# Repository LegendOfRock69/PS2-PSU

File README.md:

## PS2-PSU
The PS2-PSU is a custom regulator solution meant for powering Playstation 2 Slims that have had an Advanced Trim performed to them or untrimmed consoles with the existing power regulatory components removed.

## Disclaimer
This is **NOT** a "drop-in" power regulator solution for portable PS2's. This board is meant to **only** be powered externally via USB-C and should not be powered by a battery. It is meant to power PS2's that have been trimmed and require the [Advanced Trim voltage relocations](https://bitbuilt.net/forums/index.php?threads/the-definitive-ps2-trimming-guide.1841/); or PS2's that have had their existing power regulating components removed. This board has only been tested with a SCPH-79001 motherboard so far but should work with any SCPH-7900X PS2 Slim; or any Playstation 2 Slim that requires the necessary voltages. Revision 2 is planned to be a full "drop-in" solution to use for portables in conjunction with a separate battery protection PCB and will be released soon.

This board has **only** been tested with the [Adafuit 5803](https://www.mouser.ca/ProductDetail/Adafruit/5803?qs=QpmGXVUTftHXtVI1Nl%252BHoQ%3D%3D) 5V 4A output wall adapter outlined in the BOM but any USB-C charger should work as long as it can output at least 3A or more. It is also **strongly** recommended to only use 5V to power this board as the main TPS62A06DRLR regulators have a maximum input voltage rating of 5.5v and anything higher can and will have the potential to damage the components.

## Features
- Board Dimentions: 61mm x 25mm
- Powered via USB-C
- Uses more standard voltages and 1 less regulator as opposed to the voltages recommended in the PS2 Trimming Guide

## Gallery

## Order & Assembly
- The gerber files can be uploaded to any PCB manufacturer of your choice for ordering
- While it is recommended to order this board with an ENIG surface finish, a HASL(with lead) finish will work as well
- It is **strongly** recommended to order a stencil for assembly and it is not recommended to hand solder the components
- There are 3 BOM file types included: a .xlsx BOM, a .pdf BOM and an iBOM.html
- The Bill of Materials for this board were ordered from Mouser however components can be ordered from the supplier of your choice so long as they are stocked. links to a supplier were left out in the BOM for users who may prefer a different supplier
- As per the disclaimer, the Adafruit 5803 outlined in the BOM is recommended for not only its voltage and amperage output, but it also has an external switch to utilize as the board will be powered once plugged in if not using an external switch

## Installation
Whereas the PS2-PSU uses more standard voltages than the those outlined in the [Definitive PS2 Trimming Guide](https://bitbuilt.net/forums/index.php?threads/the-definitive-ps2-trimming-guide.1841/), the connections are as follows:

- 1V on the PSU is required to be connected to the PS2's 1.25V area
- 1V8 on the PSU is required to be connected to **BOTH** the PS2's 1.75V **and** 2.5V areas
- 3V3 on the PSU is required to be connected to the PS2's 3.5V area
- 5V on the PSU is required to be connected to the PS2's 5V area

**Please note that all volatge relocations MUST be connected together on a trimmed PS2 as trimming cuts away the internal voltage layers that connects them together**

SCPH-79001 and alike (please note that the 2 8-pin IC's circled in red must be removed if they are present) 

SCPH-79003 and alike 

When using this PSU or any custom regulator solution to externally power a PS2, 3.5V (or 3V3) must be reconnected to this area on the 8-pin ic. If the 8-pin ic is not present, 3.5v (or 3V3) must be connected to the small capacitor above it 

5V **must** be connected to the orange area in this photo as it powers both the DAC and the Ethernet IC and is a requirement for the PS2 to boot 

## License
[Solderpad Hardware License v2.1](https://solderpad.org/licenses/SHL-2.1/)

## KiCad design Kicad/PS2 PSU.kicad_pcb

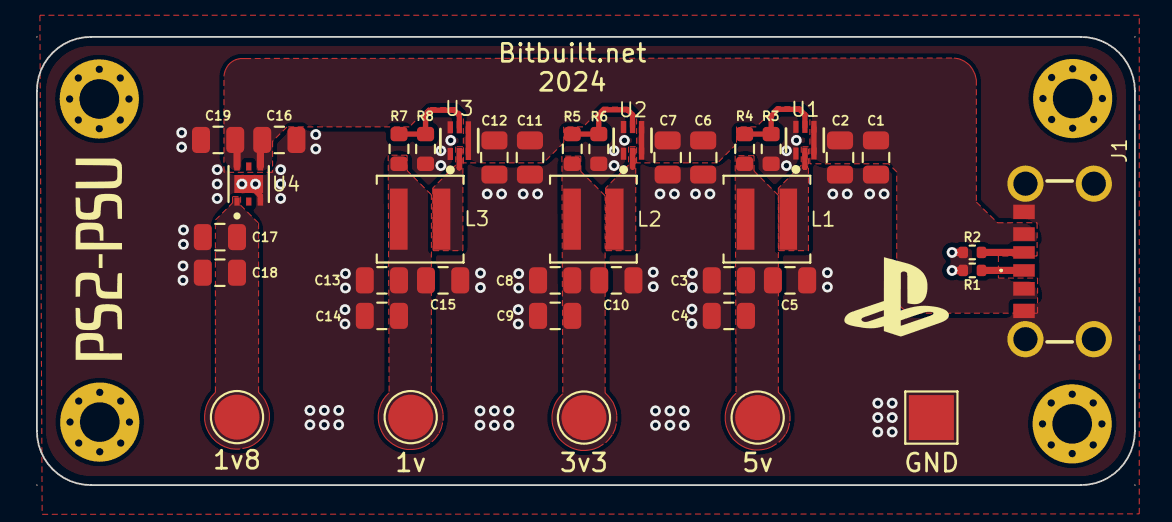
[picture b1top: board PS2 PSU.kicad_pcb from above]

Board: 2 copper layers, 61.0 x 24.9 mm, 40 parts (0 on the bottom side), 14 nets.

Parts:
1v, 1v8, 3v3, 5v: TestPoint; TestPoint_Pad_D2.5mm
C1, C2, C3, C4, C5, C6, C7, C8, C9, C10, C11, C12, C13, C14, C15, C17, C18: 22uF; C_0805_2012Metric
C16, C19: 10uF; C_0805_2012Metric
GND: TestPoint; TestPoint_Pad_2.5x2.5mm
J1: USB4125-GF-A; USB4125GFA
L1, L2: 2.2uH; L_Coilcraft_XAL4020-XXX
L3: 1uH; L_Coilcraft_XAL4020-XXX
R1, R2: 5.1k; R_0402_1005Metric
R3, R6, R8: 10k; R_0603_1608Metric
R4: 73.2k; R_0603_1608Metric
R5: 45k; R_0603_1608Metric
R7: 6.8k; R_0603_1608Metric
U1, U2, U3: TPS62A06DRLR
U4: TLV75718PDRVR

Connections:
1v: 1v.1, C13.1, C14.1, C15.1, L3.2, R7.1
1v8: 1v8.1, C17.1, C18.1, U4.1 (OUT)
3v3: 3v3.1, C8.1, C9.1, C10.1, L2.2, R5.1
5v: 5v.1, C3.1, C4.1, C5.1, L1.2, R4.1
GND: C1.2, C2.2, C3.2, C4.2, C5.2, C6.2, C7.2, C8.2, C9.2, C10.2, C11.2, C12.2, C13.2, C14.2, C15.2, C16.2, C17.2, C18.2, C19.2, GND.1, J1.A12 (GND_1), J1.B12 (GND_2), J1.MH1, J1.MH2, J1.MH3, J1.MH4, R1.2, R2.2, R3.1, R6.1, R8.1, U1.1 (GND), U1.6 (PG), U2.1 (GND), U2.6 (PG), U3.1 (GND), U3.6 (PG), U4.3 (GND), U4.7 (EXP)
unnamed: J1.A5 (CC1), R1.1
unnamed: J1.B5 (CC2), R2.1
unnamed: R3.2, R4.2, U1.5 (FB)
unnamed: L1.1, U1.2 (SW)
unnamed: R5.2, R6.2, U2.5 (FB)
unnamed: L2.1, U2.2 (SW)
unnamed: R7.2, R8.2, U3.5 (FB)
unnamed: L3.1, U3.2 (SW)
VIN: C1.1, C2.1, C6.1, C7.1, C11.1, C12.1, C16.1, C19.1, J1.A9 (VBUS_1), J1.B9 (VBUS_2), U1.3 (VIN), U1.4 (EN), U2.3 (VIN), U2.4 (EN), U3.3 (VIN), U3.4 (EN), U4.4 (EN), U4.6 (IN)

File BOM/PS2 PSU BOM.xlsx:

Item # | Reference Designator | Quantity | Manufacturer | Mfr. Part # | Description | Package | Type
1.0 | U1, U2, U3 | 3.0 | Texas Instruments | TPS62A06DRLR | Switching Voltage Regulators 2.5-V to 5.5-V input, 6-A high-efficiency step-dow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 | SOT-563-6 | SMD/SMT
2.0 | U4 | 1.0 | Texas Instruments | TLV75718PDRVR | LDO Voltage Regulators 1-A, low-IQ high-accuracy low-dropout (LDO) voltage regu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 | WSON-6 | SMD/SMT
3.0 | L1, L2 | 2.0 | Coilcraft | XAL4020-222MEC | Power Inductors - SMD 2.2uH Shld 20% 5.5A 38.7mOhms AECQ2 | 1616 (4040 metric) | SMD/SMT
4.0 | L3 | 1.0 | Coilcraft | XAL4020-102MEC | Power Inductors - SMD 1uH Shld 20% 9.6A 14.6mOhms AECQ2 | 1616 (4040 metric) | SMD/SMT
5.0 | C1 - C15, C17, C18 | 17.0 | Murata Electronics | GRM21BZ71A226ME15L | Multilayer Ceramic Capacitors MLCC - SMD/SMT 22 uF 10 VDC 20% 0805 X7R | 0805 (2012 metric) | SMD/SMT
6.0 | C16, C19 | 2.0 | Murata Electronics | GCM21BR71A106KE22L | Multilayer Ceramic Capacitors MLCC - SMD/SMT 10 uF 10 VDC 10% 0805 X7R AEC-Q200 | 0805 (2012 metric) | SMD/SMT
7.0 | R3, R6, R8 | 3.0 | YAGEO | RP0603BRD0710KL | Thin Film Resistors - SMD 1/10 Wa 10K Ohm 0.1% 0603 AEC-Q200 | 0603 (1608 metric) | SMD/SMT
8.0 | R1, R2 | 2.0 | YAGEO | RP0402BRD075K1L | Thin Film Resistors - SMD 1/16Wa 5.1K Ohm 0.1% 0402 AEC-Q200 | 0402 (1005 metric) | SMD/SMT
9.0 | R4 | 1.0 | YAGEO | RT0603BRD0773K2L | Thin Film Resistors - SMD 1/10W 73.2K ohm .1% 25ppm | 0603 (1608 metric) | SMD/SMT
10.0 | R5 | 1.0 | YAGEO | RT0603BRE0745K3L | Thin Film Resistors - SMD 45.3 kOhms 50PPM/C 100mW 0603 10% | 0603 (1608 metric) | SMD/SMT
11.0 | R7 | 1.0 | YAGEO | RT0603BRD076K8L | Thin Film Resistors - SMD 1/10W 6.8K ohm .1% 25ppm | 0603 (1608 metric) | SMD/SMT
12.0 | J1 | 1.0 | GCT | USB4125-GF-A | USB Connectors USB C Rec, GF, RA, 6p, SMT, TH stakes, H = 3.16mm, T+R | N/A | SMD/SMT
13.0 | N/A | 1.0 | Adafruit | 5803.0 | Wall Mount AC Adapters Wall Power Supply with USB C - 5V 4A Output and Switch | N/A | N/A

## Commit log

2024-12-08 Create License
2024-12-08 Updated LICENSE
